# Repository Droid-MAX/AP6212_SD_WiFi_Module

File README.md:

# AP6212_SD_WiFi_Module
ap6212 wireless card module using sdio interface.

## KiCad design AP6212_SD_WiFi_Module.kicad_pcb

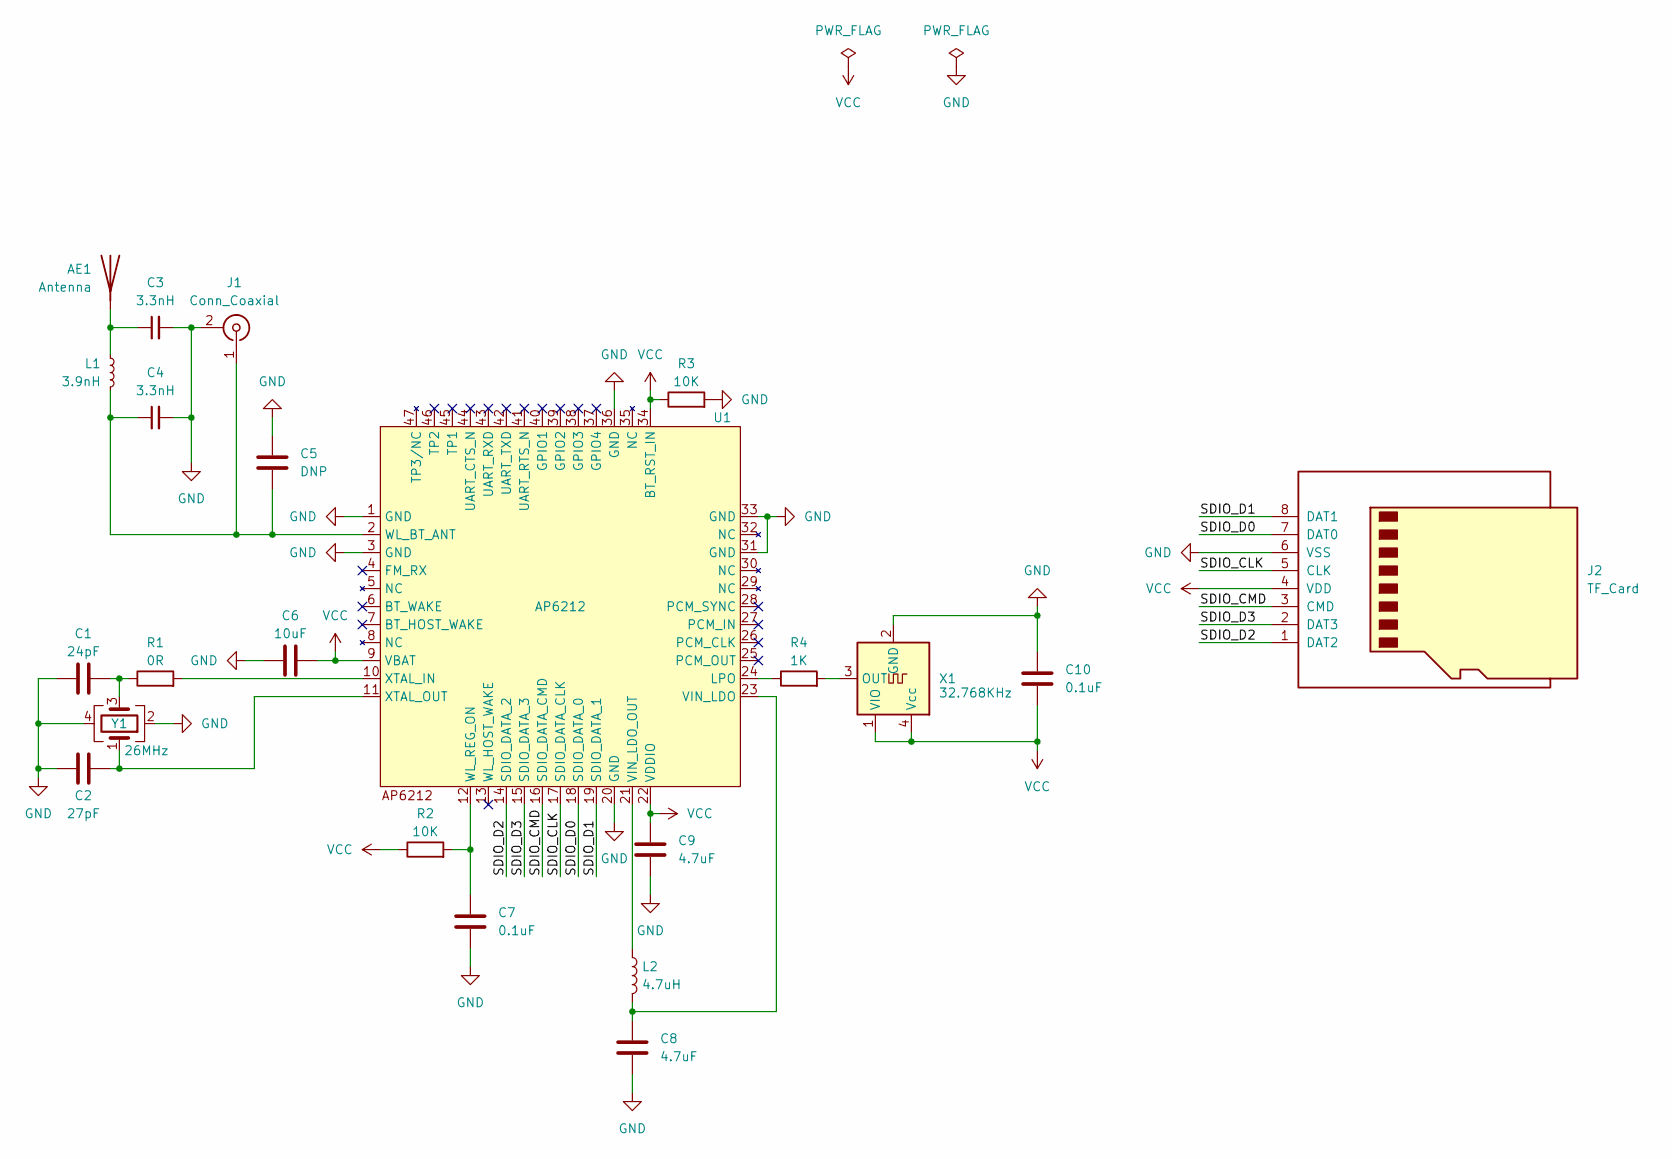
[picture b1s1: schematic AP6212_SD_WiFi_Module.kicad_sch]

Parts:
AE1: Antenna; AT7020-E3R0
C1: 24pF; C_0603_1608Metric
C2: 27pF; C_0603_1608Metric
C3, C4: 3.3nH; C_0402_1005Metric
C5: DNP; C_0402_1005Metric
C6: 10uF; C_0603_1608Metric
C7, C10: 0.1uF; C_0603_1608Metric
C8, C9: 4.7uF; C_0603_1608Metric
J1: Conn_Coaxial; U.FL_Hirose_U.FL-R-SMT-1_Vertical
J2: TF_Card; TFCARD
L1: 3.9nH; L_0402_1005Metric
L2: 4.7uH; IND-SMD_L2.5-W2.0
R1: 0R; R_0603_1608Metric
R2, R3: 10K; R_0603_1608Metric
R4: 1K; R_0603_1608Metric
U1: AP6212
X1: 32.768KHz; Crystal_SMD_3225-4Pin_3.2x2.5mm
Y1: 26MHz; Crystal_SMD_3225-4Pin_3.2x2.5mm

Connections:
/SDIO_CLK: J2.5 (CLK), U1.17 (SDIO_DATA_CLK)
/SDIO_CMD: J2.3 (CMD), U1.16 (SDIO_DATA_CMD)
/SDIO_D0: J2.7 (DAT0), U1.18 (SDIO_DATA_0)
/SDIO_D1: J2.8 (DAT1), U1.19 (SDIO_DATA_1)
/SDIO_D2: J2.1 (DAT2), U1.14 (SDIO_DATA_2)
/SDIO_D3: J2.2 (DAT3), U1.15 (SDIO_DATA_3)
GND: C1.1, C2.1, C3.2, C4.2, C5.1, C6.1, C7.2, C8.2, C9.2, C10.1, J1.2 (Ext), J2.6 (VSS), R3.2, U1.1 (GND), U1.3 (GND), U1.20 (GND), U1.31 (GND), U1.33 (GND), U1.36 (GND), X1.2 (GND), Y1.2, Y1.4
unnamed: AE1.1 (A), C3.1, L1.2
unnamed: C1.2, R1.1, Y1.3
unnamed: C4.1, C5.2, J1.1 (In), L1.1, U1.2 (WL_BT_ANT)
unnamed: R4.1, U1.24 (LPO)
unnamed: C8.1, L2.2, U1.23 (VIN_LDO)
unnamed: L2.1, U1.21 (VIN_LDO_OUT)
unnamed: C7.1, R2.2, U1.12 (WL_REG_ON)
unnamed: R1.2, U1.10 (XTAL_IN)
unnamed: C2.2, U1.11 (XTAL_OUT), Y1.1
unnamed: R4.2, X1.3 (OUT)
VCC: C6.2, C9.1, C10.2, J2.4 (VDD), R2.1, R3.1, U1.9 (VBAT), U1.22 (VDDIO), U1.34 (BT_RST_IN), X1.1 (VIO), X1.4 (Vcc)

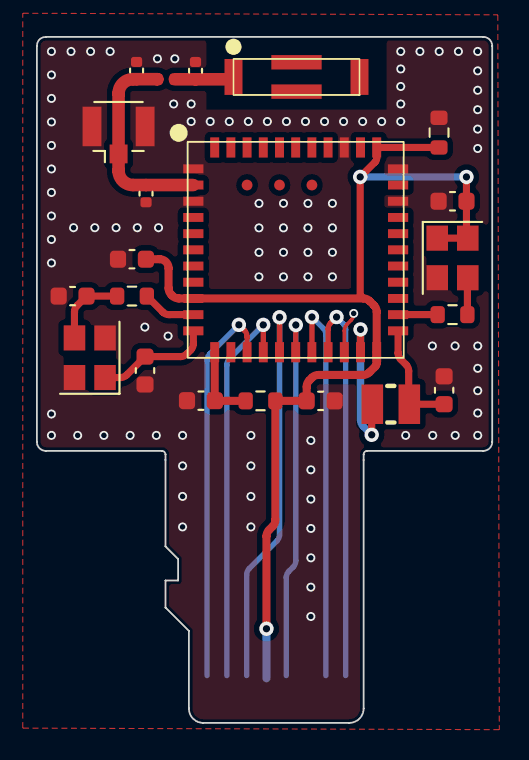
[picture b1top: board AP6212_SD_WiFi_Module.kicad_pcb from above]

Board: 2 copper layers, 25.3 x 38.1 mm, 22 parts (1 on the bottom side), 18 nets.

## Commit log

2023-08-21 first release
2023-08-21 feat: Change the crystal package to SMD 3225
2023-08-21 feat: Fixed test point silkscreen
2023-08-22 feat: Components layout adjustment
2023-08-22 feat: Set constraint rules and fine-tune layout
2023-08-22 feat: Optimized layout and routing
2023-08-22 feat: Determine the final pcb shape and adjust part of the gnd hole position
2023-08-22 feat: Optimized antenna layout and routing
2023-08-23 feat: Fine-tune the antenna layout and remove all teardrops
2023-08-23 feat: Fine-tune part of gnd vias position
2023-08-23 feat: The antenna line width is modified to 0.7 mm, and some gnd through holes are added
2023-08-23 feat: Part shape correction of tf card
2023-08-23 feat: Fixed tf-card silk screen errors
2023-08-23 feat: Add teardrop to test point pads
2023-08-25 feat: Replace 4.7uH inductor package to VLS252012
2023-08-26 feat: Replace 4.7uH inductor package to SWPA252012
2023-08-27 feat: Modify the C7 parameter value of 0.1 uF
2023-08-27 feat: Removed the test point and completed the LPO part of the peripheral circuit
2023-09-06 feat: Increase the length of tf card body
2023-10-29 BT_RST_N must be driven high or low(not left floating)
